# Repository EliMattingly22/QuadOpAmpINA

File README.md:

# QuadOpAmpINA
A PCB to adapt a quad opamp package to a standard (Rg, pins 1-8) INA DIP package

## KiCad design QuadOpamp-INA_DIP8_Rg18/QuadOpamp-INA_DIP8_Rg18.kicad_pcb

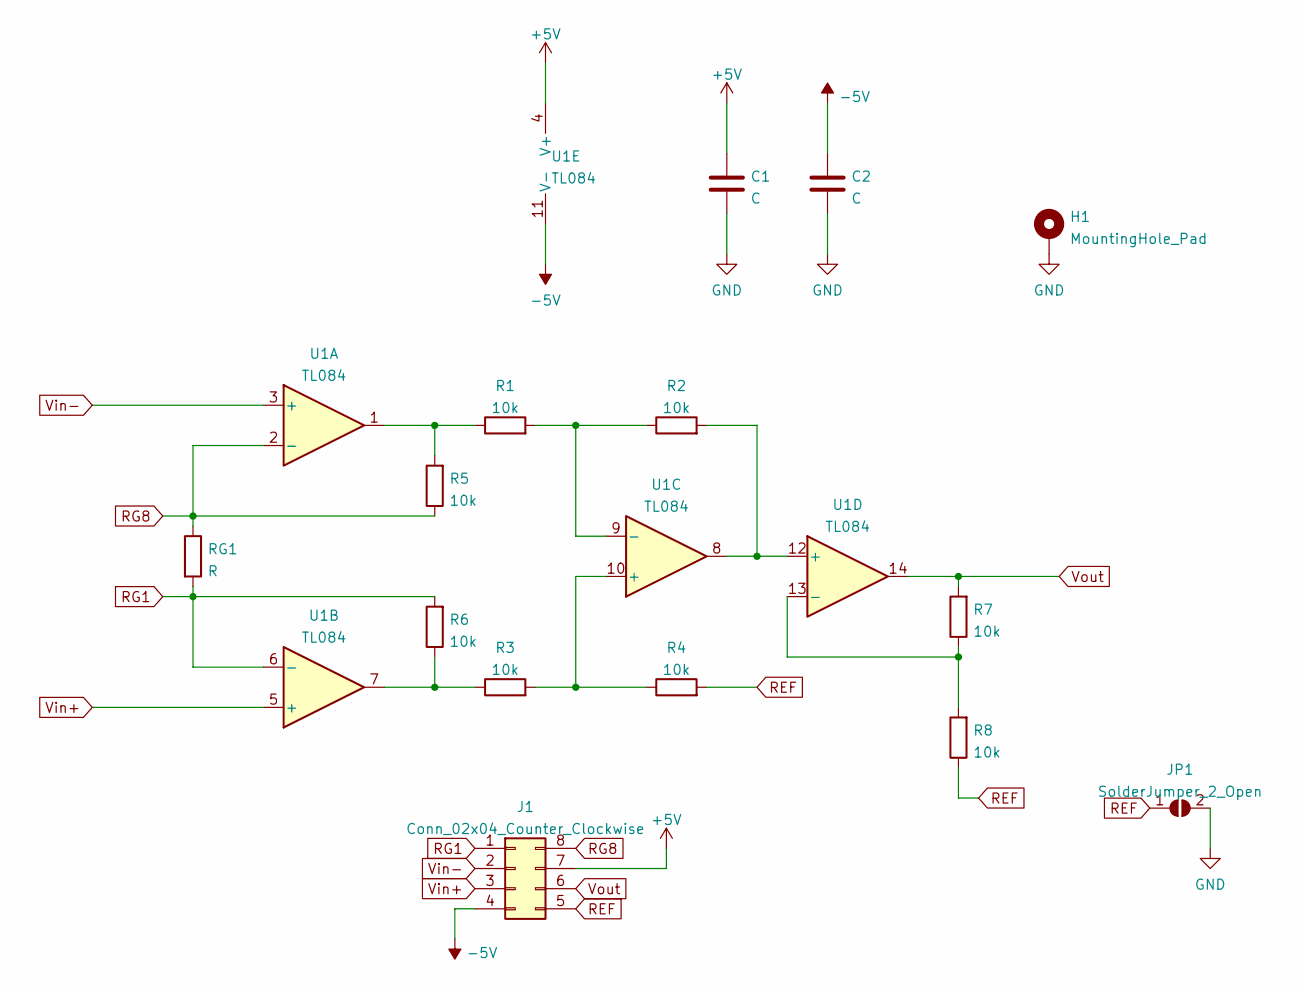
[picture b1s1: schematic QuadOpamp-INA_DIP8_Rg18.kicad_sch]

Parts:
C1, C2: C; C_0805_2012Metric
H1: MountingHole_Pad; MountingHole_2.2mm_M2_DIN965_Pad
J1: Conn_02x04_Counter_Clockwise; DIP-8_W7.62mm
JP1: SolderJumper_2_Open; SolderJumper-2_P1.3mm_Open_RoundedPad1.0x1.5mm
R1, R2, R3, R4, R5, R6, R7, R8: 10k; R_0805_2012Metric
RG1: R; R_0805_2012Metric
U1: TL084; TSSOP-14_4.4x5mm_P0.65mm

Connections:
+5V: C1.1, J1.7, U1.4 (V+)
-5V: C2.1, J1.4, U1.11 (V-)
GND: C1.2, C2.2, H1.1, JP1.2 (B)
unnamed: R1.1, R5.2, U1.1
unnamed: R1.2, R2.1, U1.9 (-)
unnamed: R2.2, U1.8, U1.12 (+)
unnamed: R3.2, R4.1, U1.10 (+)
unnamed: R3.1, R6.1, U1.7
unnamed: R7.1, R8.2, U1.13 (-)
REF: J1.5, JP1.1 (A), R4.2, R8.1
RG1: J1.1, R6.2, RG1.2, U1.6 (-)
RG8: J1.8, R5.1, RG1.1, U1.2 (-)
Vin+: J1.3, U1.5 (+)
Vin-: J1.2, U1.3 (+)
Vout: J1.6, R7.2, U1.14

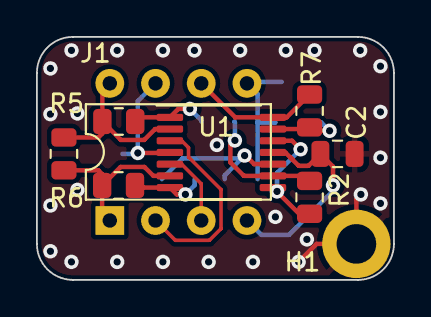
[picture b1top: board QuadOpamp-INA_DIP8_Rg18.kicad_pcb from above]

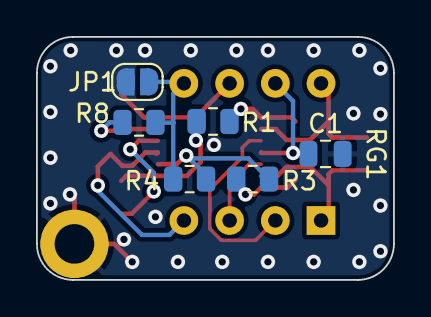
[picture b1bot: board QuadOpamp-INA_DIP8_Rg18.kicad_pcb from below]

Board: 2 copper layers, 19.8 x 13.5 mm, 15 parts (6 on the bottom side), 15 nets.

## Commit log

2022-01-11 Gerbers
